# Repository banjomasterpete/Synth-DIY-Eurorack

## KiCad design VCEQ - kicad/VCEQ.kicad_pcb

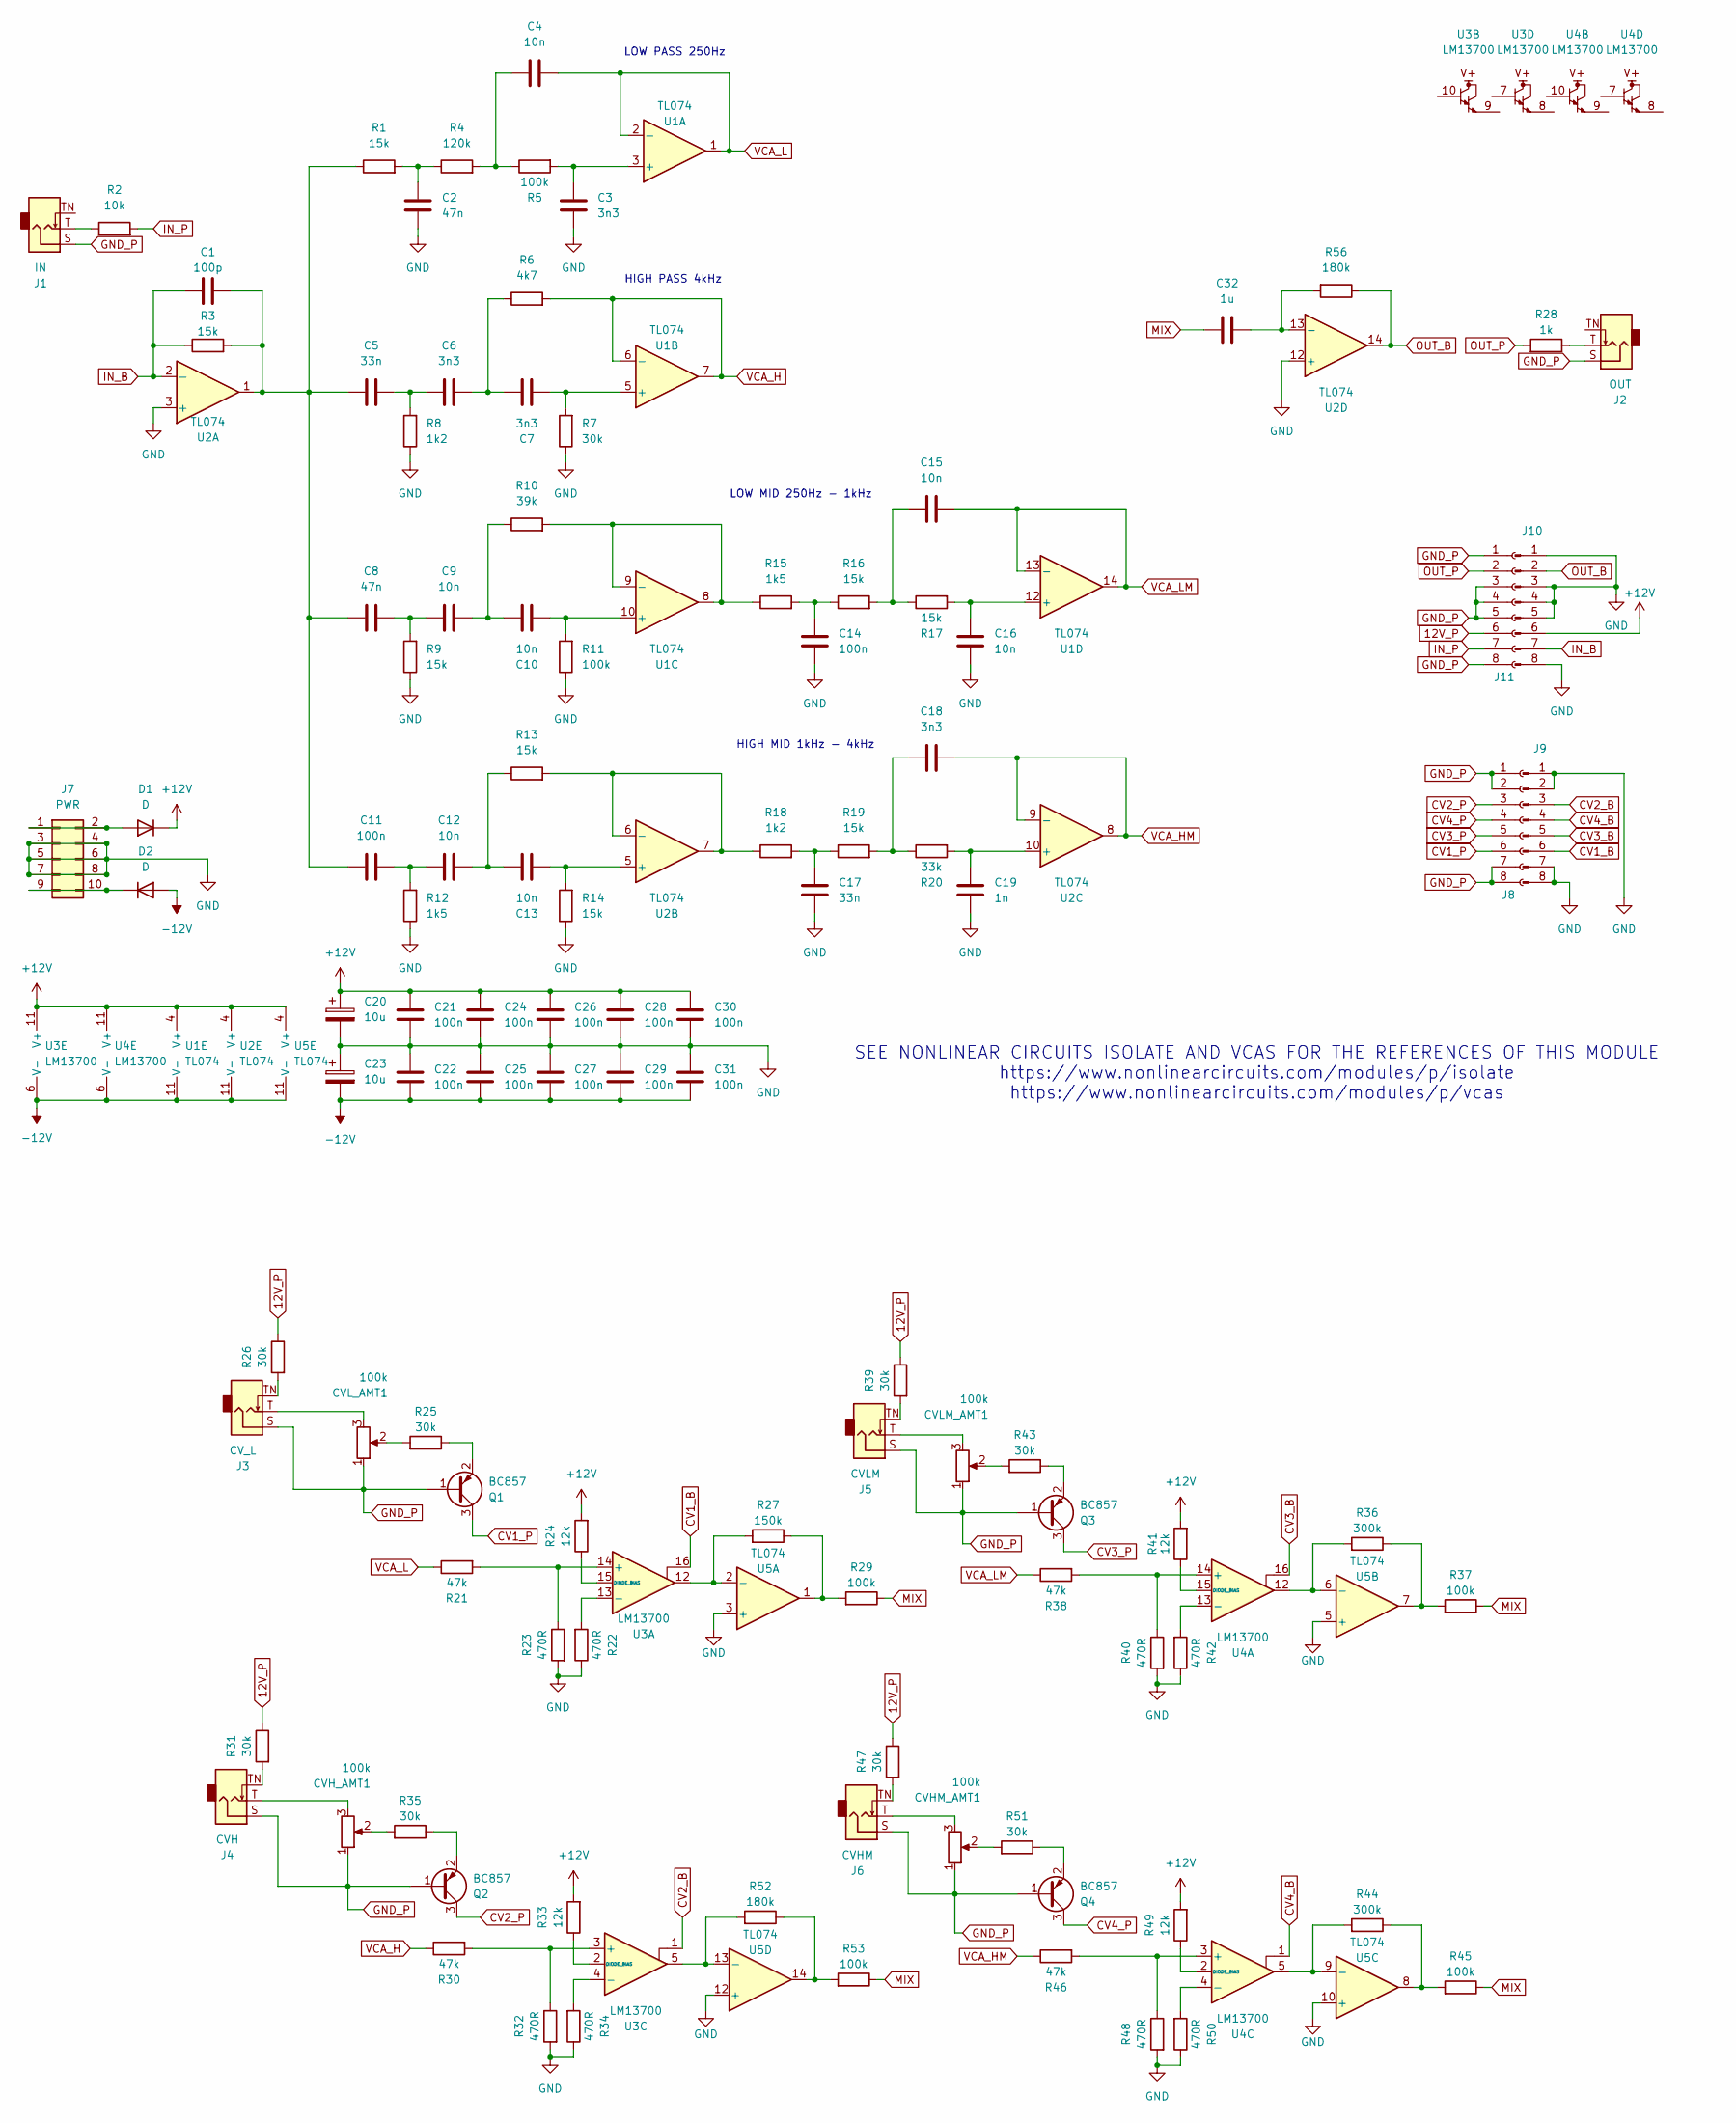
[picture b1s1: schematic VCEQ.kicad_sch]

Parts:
C1: 100p; C_0805_2012Metric_Pad1.18x1.45mm_HandSolder
C2, C8: 47n; C_0805_2012Metric_Pad1.18x1.45mm_HandSolder
C3, C6, C7, C18: 3n3; C_0805_2012Metric_Pad1.18x1.45mm_HandSolder
C4, C9, C10, C12, C13, C15, C16: 10n; C_0805_2012Metric_Pad1.18x1.45mm_HandSolder
C5, C17: 33n; C_0805_2012Metric_Pad1.18x1.45mm_HandSolder
C11, C14, C21, C22, C24, C25, C26, C27, C28, C29, C30, C31: 100n; C_0805_2012Metric_Pad1.18x1.45mm_HandSolder
C19: 1n; C_0805_2012Metric_Pad1.18x1.45mm_HandSolder
C20, C23: 10u; CP_Radial_D5.0mm_P2.50mm
C32: 1u; C_0805_2012Metric_Pad1.18x1.45mm_HandSolder
CVHM_AMT1: 100k; Potentiometer_Alps_RK09K_Single_Vertical
CVH_AMT1: 100k; Potentiometer_Alps_RK09K_Single_Vertical
CVLM_AMT1: 100k; Potentiometer_Alps_RK09K_Single_Vertical
CVL_AMT1: 100k; Potentiometer_Alps_RK09K_Single_Vertical
D1, D2: D; D_1210_3225Metric_Pad1.42x2.65mm_HandSolder
J1: IN; Jack_3.5mm_QingPu_WQP-PJ398SM_Vertical
J2: OUT; Jack_3.5mm_QingPu_WQP-PJ398SM_Vertical
J3: CV_L; Jack_3.5mm_QingPu_WQP-PJ398SM_Vertical
J4: CVH; Jack_3.5mm_QingPu_WQP-PJ398SM_Vertical
J5: CVLM; Jack_3.5mm_QingPu_WQP-PJ398SM_Vertical
J6: CVHM; Jack_3.5mm_QingPu_WQP-PJ398SM_Vertical
J7: PWR; PinHeader_2x05_P2.54mm_Vertical
J8, J11: PinHeader_1x08_P2.54mm_Vertical
J9, J10: Conn_01x08_Pin; PinHeader_1x08_P2.54mm_Vertical
Q1, Q2, Q3, Q4: BC857; SOT-23
R1, R3, R9, R13, R14, R16, R17, R19: 15k; R_0805_2012Metric_Pad1.20x1.40mm_HandSolder
R2: 10k; R_0805_2012Metric_Pad1.20x1.40mm_HandSolder
R4: 120k; R_0805_2012Metric_Pad1.20x1.40mm_HandSolder
R5, R11, R29, R37, R45, R53: 100k; R_0805_2012Metric_Pad1.20x1.40mm_HandSolder
R6: 4k7; R_0805_2012Metric_Pad1.20x1.40mm_HandSolder
R7, R25, R26, R31, R35, R39, R43, R47, R51: 30k; R_0805_2012Metric_Pad1.20x1.40mm_HandSolder
R8, R18: 1k2; R_0805_2012Metric_Pad1.20x1.40mm_HandSolder
R10: 39k; R_0805_2012Metric_Pad1.20x1.40mm_HandSolder
R12, R15: 1k5; R_0805_2012Metric_Pad1.20x1.40mm_HandSolder
R20: 33k; R_0805_2012Metric_Pad1.20x1.40mm_HandSolder
R21, R30, R38, R46: 47k; R_0805_2012Metric_Pad1.20x1.40mm_HandSolder
R22, R23, R32, R34, R40, R42, R48, R50: 470R; R_0805_2012Metric_Pad1.20x1.40mm_HandSolder
R24, R33, R41, R49: 12k; R_0805_2012Metric_Pad1.20x1.40mm_HandSolder
R27: 150k; R_0805_2012Metric_Pad1.20x1.40mm_HandSolder
R28: 1k; R_0805_2012Metric_Pad1.20x1.40mm_HandSolder
R36, R44: 300k; R_0805_2012Metric_Pad1.20x1.40mm_HandSolder
R52, R56: 180k; R_0805_2012Metric_Pad1.20x1.40mm_HandSolder
U1, U2, U5: TL074; SOIC-14_3.9x8.7mm_P1.27mm
U3, U4: LM13700; SOIC-16_3.9x9.9mm_P1.27mm

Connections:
12V_P: J11.6, R26.1, R31.1, R39.1, R47.1
+12V: C20.1, C21.2, C24.2, C26.2, C28.2, C30.2, D1.1 (K), J10.6, R24.2, R33.2, R41.2, R49.2, U1.4 (V+), U2.4 (V+), U3.11 (V+), U4.11 (V+), U5.4 (V+)
-12V: C22.1, C23.2, C25.1, C27.1, C29.1, C31.1, D2.2 (A), U1.11 (V-), U2.11 (V-), U3.6 (V-), U4.6 (V-), U5.11 (V-)
CV1_B: J9.6, U3.16
CV1_P: J8.6, Q1.3 (C)
CV2_B: J9.3, U3.1
CV2_P: J8.3, Q2.3 (C)
CV3_B: J9.5, U4.16
CV3_P: J8.5, Q3.3 (C)
CV4_B: J9.4, U4.1
CV4_P: J8.4, Q4.3 (C)
GND: C2.1, C3.1, C14.1, C16.1, C17.1, C19.1, C20.2, C21.1, C22.2, C23.1, C24.1, C25.2, C26.1, C27.2, C28.1, C29.2, C30.1, C31.2, J7.3, J7.4, J7.5, J7.6, J7.7, J7.8, J9.1, J9.2, J9.7, J9.8, J10.1, J10.3, J10.4, J10.5, J10.8, R7.1, R8.1, R9.1, R11.1, R12.1, R14.1, R22.1, R23.2, R32.2, R34.1, R40.2, R42.1, R48.2, R50.1, U2.3 (+), U2.12 (+), U5.3 (+), U5.5 (+), U5.10 (+), U5.12 (+)
GND_P: CVHM_AMT1.1, CVH_AMT1.1, CVLM_AMT1.1, CVL_AMT1.1, J1.S, J2.S, J3.S, J4.S, J5.S, J6.S, J8.1, J8.2, J8.7, J8.8, J11.1, J11.3, J11.4, J11.5, J11.8, Q1.1 (B), Q2.1 (B), Q3.1 (B), Q4.1 (B)
IN_B: C1.1, J10.7, R3.1, U2.2 (-)
IN_P: J11.7, R2.2
MIX: C32.2, R29.1, R37.1, R45.1, R53.1
unnamed: C1.2, C5.2, C8.2, C11.2, R1.1, R3.2, U2.1
unnamed: C2.2, R1.2, R4.1
unnamed: C4.2, R4.2, R5.1
unnamed: C5.1, C6.2, R8.2
unnamed: C6.1, C7.2, R6.1
unnamed: C8.1, C9.2, R9.2
unnamed: C9.1, C10.2, R10.1
unnamed: C11.1, C12.2, R12.2
unnamed: C12.1, C13.2, R13.1
unnamed: C14.2, R15.2, R16.1
unnamed: C15.2, R16.2, R17.1
unnamed: C17.2, R18.2, R19.1
unnamed: C18.2, R19.2, R20.1
unnamed: CVHM_AMT1.2, R51.2
unnamed: CVHM_AMT1.3, J6.T
unnamed: CVH_AMT1.2, R35.2
unnamed: CVH_AMT1.3, J4.T
unnamed: CVLM_AMT1.2, R43.2
unnamed: CVLM_AMT1.3, J5.T
unnamed: CVL_AMT1.2, R25.2
unnamed: CVL_AMT1.3, J3.T
unnamed: D1.2 (A), J7.1, J7.2
unnamed: D2.1 (K), J7.9, J7.10
unnamed: J1.T, R2.1
unnamed: J2.T, R28.1
unnamed: J3.TN, R26.2
unnamed: J4.TN, R31.2
unnamed: J5.TN, R39.2
unnamed: J6.TN, R47.2
unnamed: Q1.2 (E), R25.1
unnamed: Q2.2 (E), R35.1
unnamed: Q3.2 (E), R43.1
unnamed: Q4.2 (E), R51.1
unnamed: R27.1, R29.2, U5.1
unnamed: R36.1, R37.2, U5.7
unnamed: R44.1, R45.2, U5.8
unnamed: R52.1, R53.2, U5.14
unnamed: C3.2, R5.2, U1.3 (+)
unnamed: C7.1, R7.2, U1.5 (+)
unnamed: C10.1, R11.2, U1.10 (+)
unnamed: R10.2, R15.1, U1.8, U1.9 (-)
unnamed: C16.2, R17.2, U1.12 (+)
unnamed: C13.1, R14.2, U2.5 (+)
unnamed: R13.2, R18.1, U2.6 (-), U2.7
unnamed: C19.2, R20.2, U2.10 (+)
unnamed: C32.1, R56.2, U2.13 (-)
unnamed: R21.2, R23.1, U3.14 (+)
unnamed: R22.2, U3.13 (-)
unnamed: R24.1, U3.15 (DIODE_BIAS)
unnamed: R30.2, R32.1, U3.3 (+)
unnamed: R34.2, U3.4 (-)
unnamed: R33.1, U3.2 (DIODE_BIAS)
unnamed: R38.2, R40.1, U4.14 (+)
unnamed: R42.2, U4.13 (-)
unnamed: R41.1, U4.15 (DIODE_BIAS)
unnamed: R46.2, R48.1, U4.3 (+)
unnamed: R50.2, U4.4 (-)
unnamed: R49.1, U4.2 (DIODE_BIAS)
unnamed: R27.2, U3.12, U5.2 (-)
unnamed: R36.2, U4.12, U5.6 (-)
unnamed: R44.2, U4.5, U5.9 (-)
unnamed: R52.2, U3.5, U5.13 (-)
OUT_B: J10.2, R56.1, U2.14
OUT_P: J11.2, R28.2
VCA_H: R6.2, R30.1, U1.6 (-), U1.7
VCA_HM: C18.1, R46.1, U2.8, U2.9 (-)
VCA_L: C4.1, R21.1, U1.1, U1.2 (-)
VCA_LM: C15.1, R38.1, U1.13 (-), U1.14

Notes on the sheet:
LOW PASS 250Hz
HIGH MID 1kHz - 4kHz
LOW MID 250Hz - 1kHz
SEE NONLINEAR CIRCUITS ISOLATE AND VCAS FOR THE REFERENCES OF THIS MODULE https://www.nonlinearcircuits.com/modules/p/isolate https://www.nonlinearcircuits.com/modules/p/vcas
HIGH PASS 4kHz

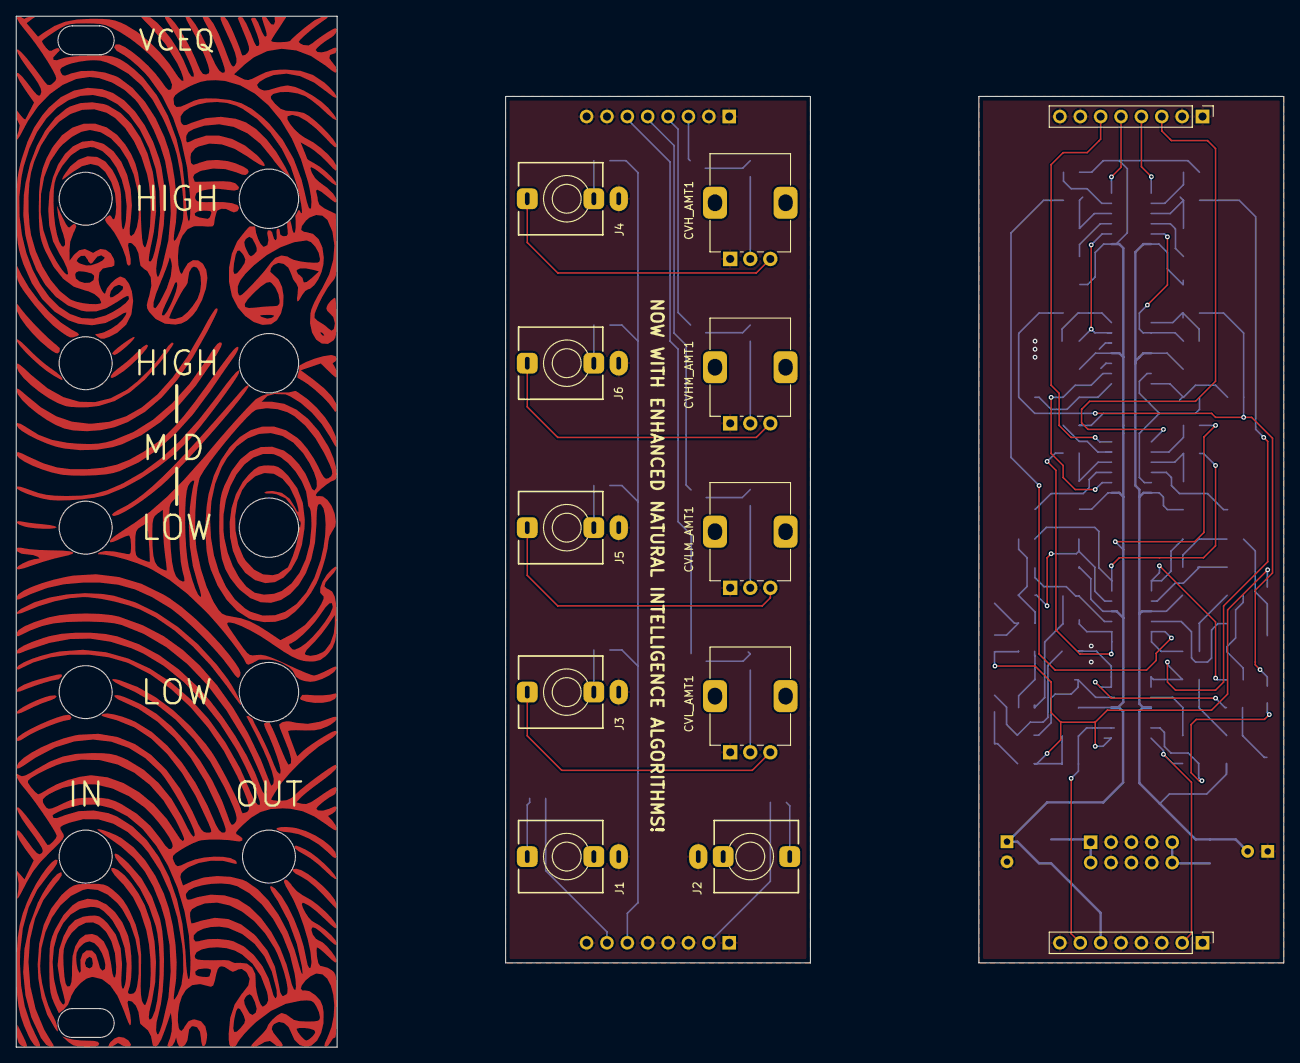
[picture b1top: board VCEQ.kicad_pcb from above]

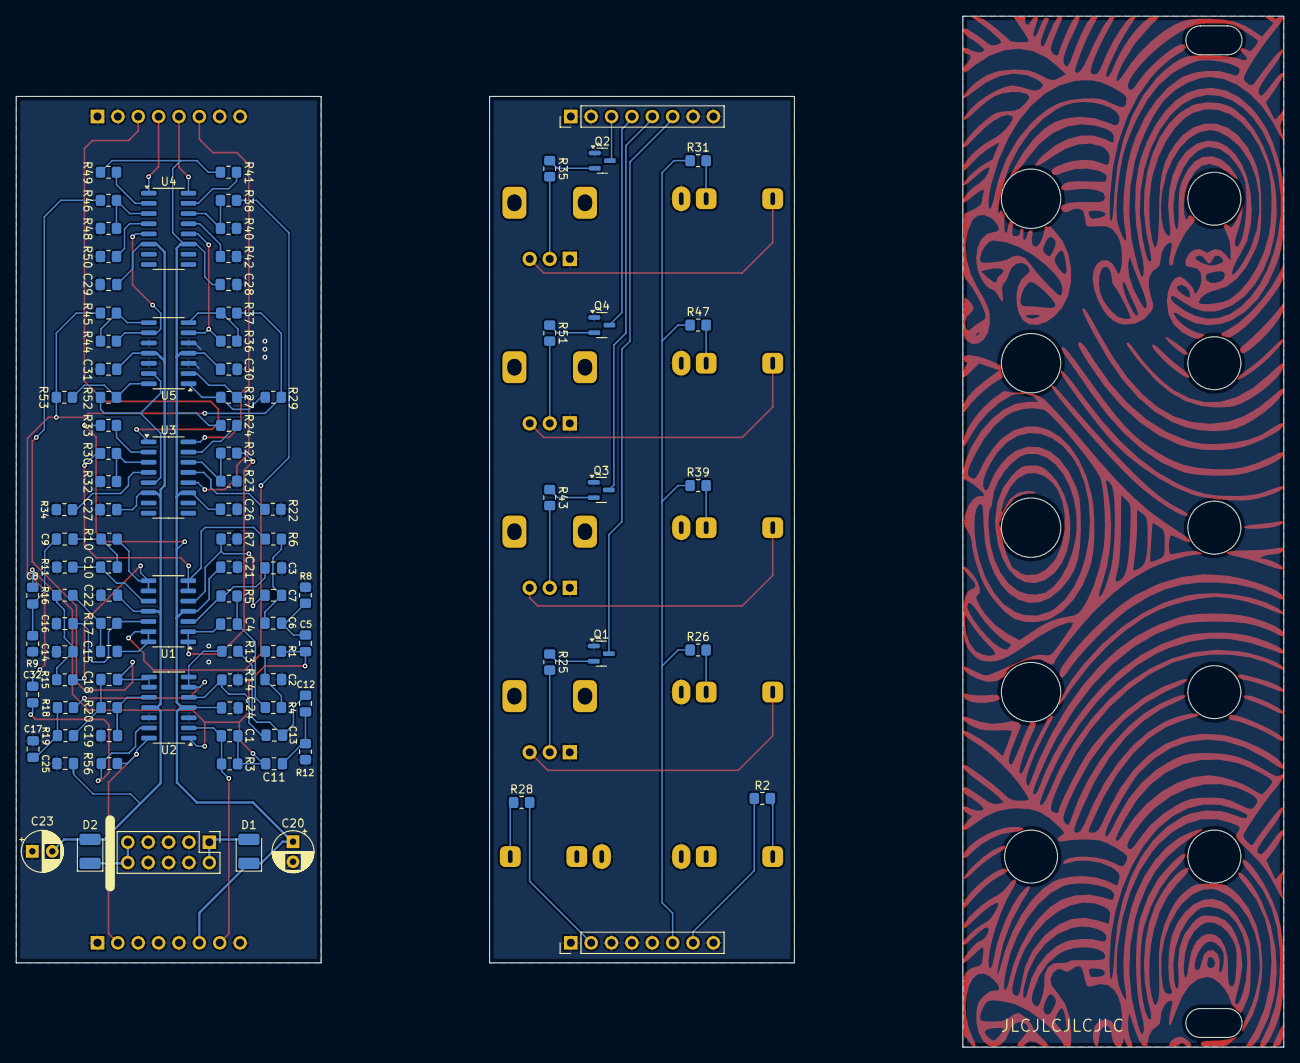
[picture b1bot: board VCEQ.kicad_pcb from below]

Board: 2 copper layers, 158.0 x 128.5 mm, 112 parts (100 on the bottom side), 84 nets.

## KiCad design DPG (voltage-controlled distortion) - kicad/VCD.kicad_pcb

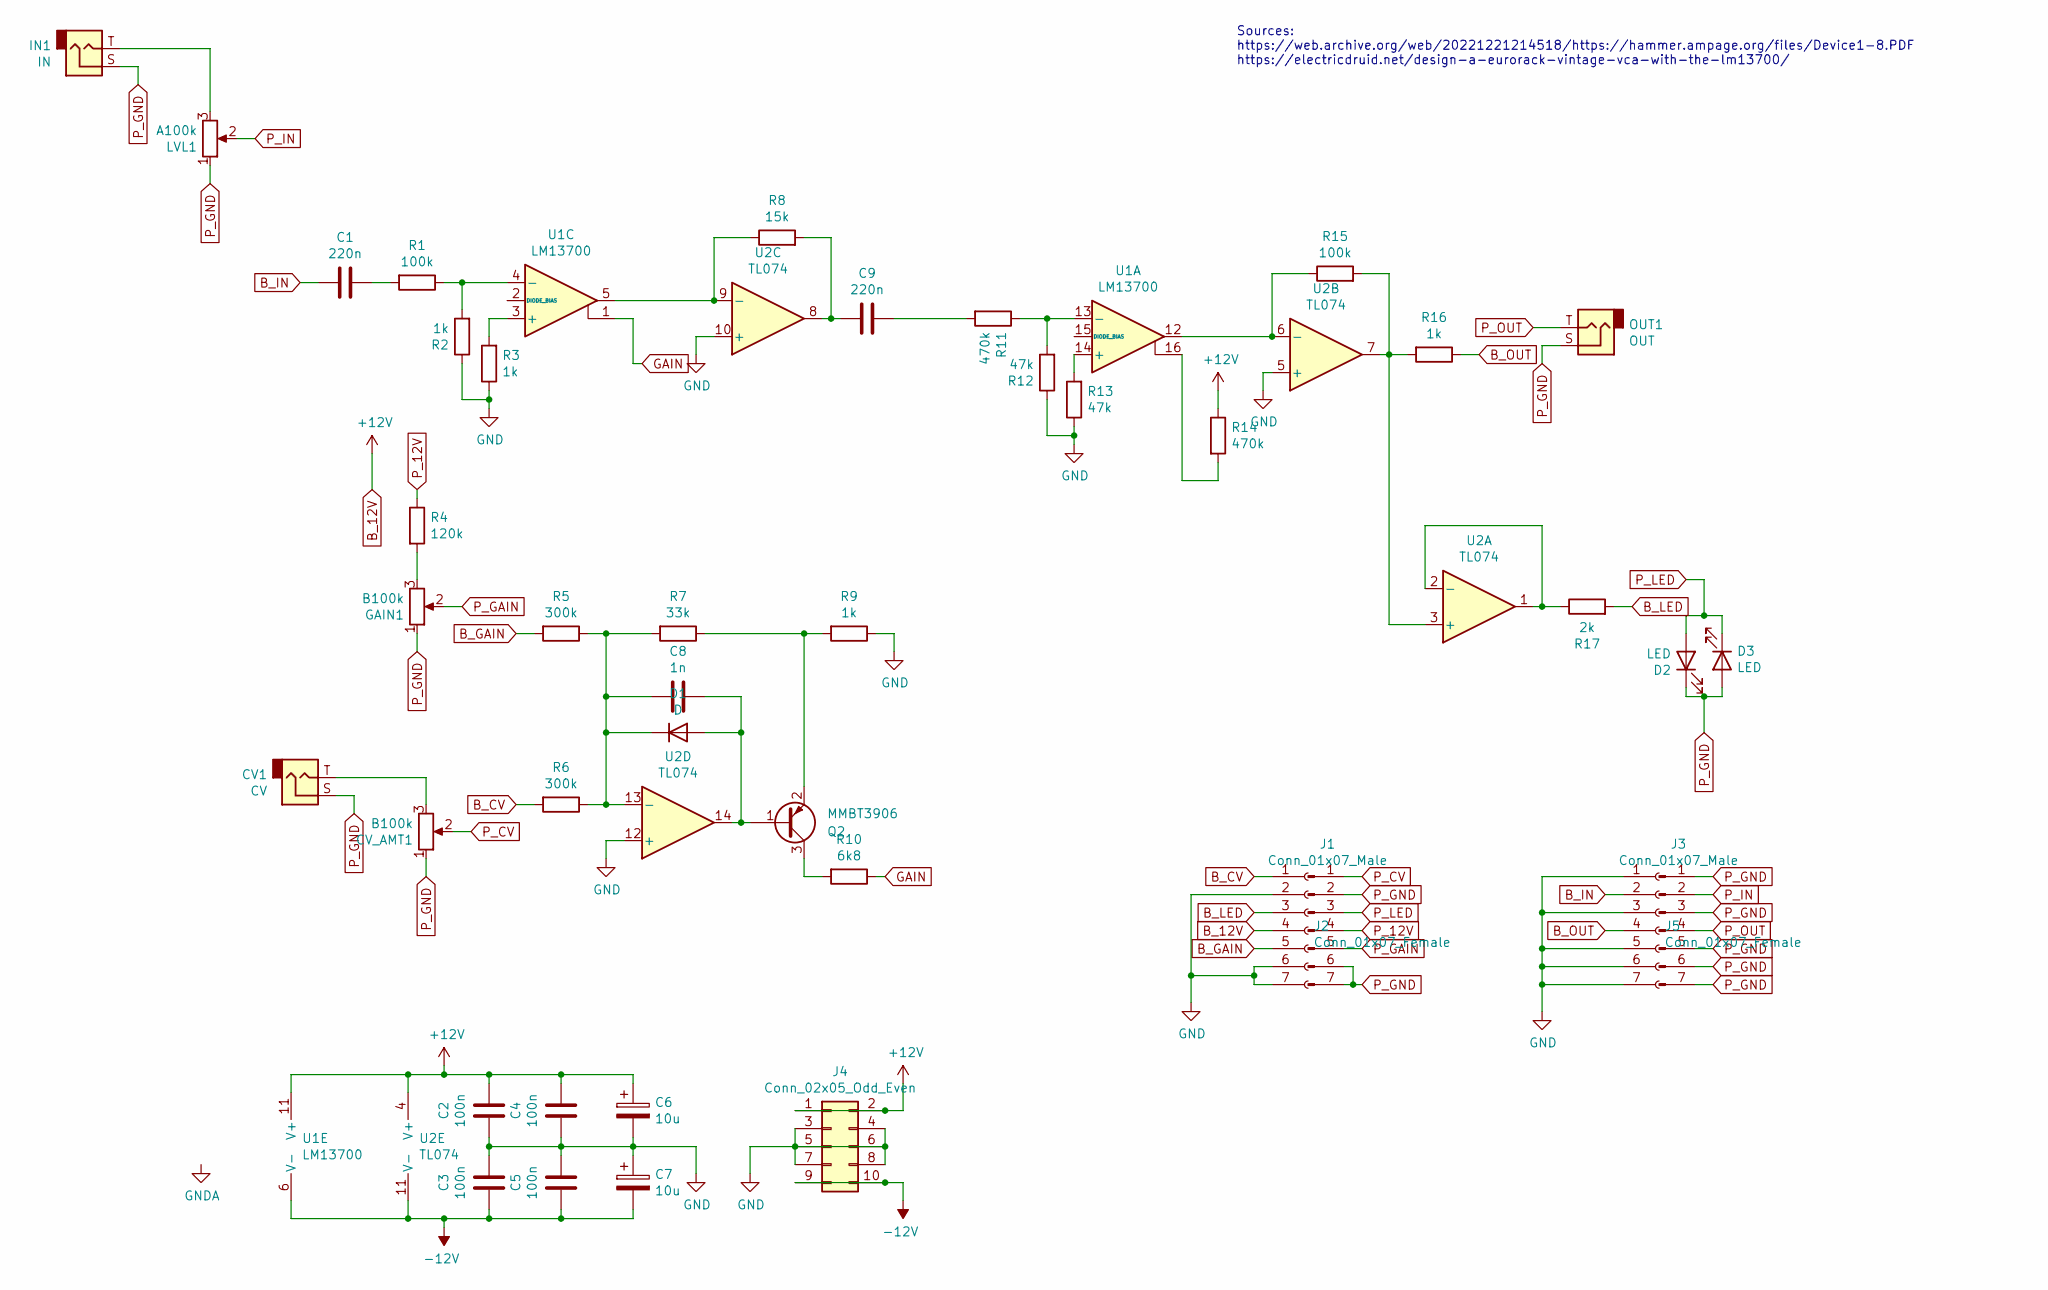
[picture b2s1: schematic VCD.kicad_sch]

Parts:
C1, C9: 220n; C_0805_2012Metric_Pad1.18x1.45mm_HandSolder
C2, C3, C4, C5: 100n; C_0805_2012Metric_Pad1.18x1.45mm_HandSolder
C6, C7: 10u; CP_Radial_D5.0mm_P2.50mm
C8: 1n; C_0805_2012Metric_Pad1.18x1.45mm_HandSolder
CV1: CV; Jack_3.5mm_QingPu_WQP-PJ366ST_Vertical
CV_AMT1: B100k; Potentiometer_Alpha_RD901F-40-00D_Single_Vertical
D1: D; D_SOD-323_HandSoldering
D2, D3: LED; LED_D3.0mm
GAIN1: B100k; Potentiometer_Alpha_RD901F-40-00D_Single_Vertical
IN1: IN; Jack_3.5mm_QingPu_WQP-PJ366ST_Vertical
J1, J3: Conn_01x07_Male; PinHeader_1x07_P2.54mm_Vertical
J2, J5: Conn_01x07_Female; PinHeader_1x07_P2.54mm_Vertical
J4: Conn_02x05_Odd_Even; PinHeader_2x05_P2.54mm_Vertical
LVL1: A100k; Potentiometer_Alpha_RD901F-40-00D_Single_Vertical
OUT1: OUT; Jack_3.5mm_QingPu_WQP-PJ366ST_Vertical
Q2: MMBT3906; SOT-23
R1, R15: 100k; R_0805_2012Metric_Pad1.20x1.40mm_HandSolder
R2, R3, R9, R16: 1k; R_0805_2012Metric_Pad1.20x1.40mm_HandSolder
R4: 120k; R_0805_2012Metric_Pad1.20x1.40mm_HandSolder
R5, R6: 300k; R_0805_2012Metric_Pad1.20x1.40mm_HandSolder
R7: 33k; R_0805_2012Metric_Pad1.20x1.40mm_HandSolder
R8: 15k; R_0805_2012Metric_Pad1.20x1.40mm_HandSolder
R10: 6k8; R_0805_2012Metric_Pad1.20x1.40mm_HandSolder
R11, R14: 470k; R_0805_2012Metric_Pad1.20x1.40mm_HandSolder
R12, R13: 47k; R_0805_2012Metric_Pad1.20x1.40mm_HandSolder
R17: 2k; R_0805_2012Metric_Pad1.20x1.40mm_HandSolder
U1: LM13700; SOIC-16_3.9x9.9mm_P1.27mm
U2: TL074; SOIC-14_3.9x8.7mm_P1.27mm

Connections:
-12V: C3.2, C5.2, C7.2, J4.9, J4.10, U1.6 (V-), U2.11 (V-)
B_12V: C2.1, C4.1, C6.1, J2.4, J4.1, J4.2, R14.1, U1.11 (V+), U2.4 (V+)
B_CV: J2.1, R6.2
B_GAIN: J2.5, R5.2
B_IN: C1.2, J5.2
B_LED: J2.3, R17.2
B_OUT: J5.4, R16.1
GAIN: R10.1, U1.1
GND: C2.2, C3.1, C4.2, C5.1, C6.2, C7.1, J2.2, J2.6, J2.7, J4.3, J4.4, J4.5, J4.6, J4.7, J4.8, J5.1, J5.3, J5.5, J5.6, J5.7, R2.1, R3.1, R9.1, R12.1, R13.1, U2.5 (+), U2.10 (+), U2.12 (+)
unnamed: C1.1, R1.2
unnamed: C9.1, R11.2
unnamed: C9.2, R8.2, U2.8
unnamed: CV1.T, CV_AMT1.3
unnamed: C8.1, D1.2 (A), Q2.1 (B), U2.14
unnamed: C8.2, D1.1 (K), R5.1, R6.1, R7.2, U2.13 (-)
unnamed: GAIN1.3, R4.2
unnamed: IN1.T, LVL1.3
unnamed: Q2.3 (C), R10.2
unnamed: Q2.2 (E), R7.1, R9.2
unnamed: R14.2, U1.16
unnamed: R13.2, U1.14 (+)
unnamed: R11.1, R12.2, U1.13 (-)
unnamed: R3.2, U1.3 (+)
unnamed: R1.1, R2.2, U1.4 (-)
unnamed: R15.2, R16.2, U2.3 (+), U2.7
unnamed: R17.1, U2.1, U2.2 (-)
unnamed: R15.1, U1.12, U2.6 (-)
unnamed: R8.1, U1.5, U2.9 (-)
P_12V: J1.4, R4.1
P_CV: CV_AMT1.2, J1.1
P_GAIN: GAIN1.2, J1.5
P_GND: CV1.S, CV_AMT1.1, D2.1 (K), D3.2 (A), GAIN1.1, IN1.S, J1.2, J1.6, J1.7, J3.1, J3.3, J3.5, J3.6, J3.7, LVL1.1, OUT1.S
P_IN: J3.2, LVL1.2
P_LED: D2.2 (A), D3.1 (K), J1.3
P_OUT: J3.4, OUT1.T

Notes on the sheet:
Sources: https://web.archive.org/web/20221221214518/https://hammer.ampage.org/files/Device1-8.PDF https://electricdruid.net/design-a-eurorack-vintage-vca-with-the-lm13700/

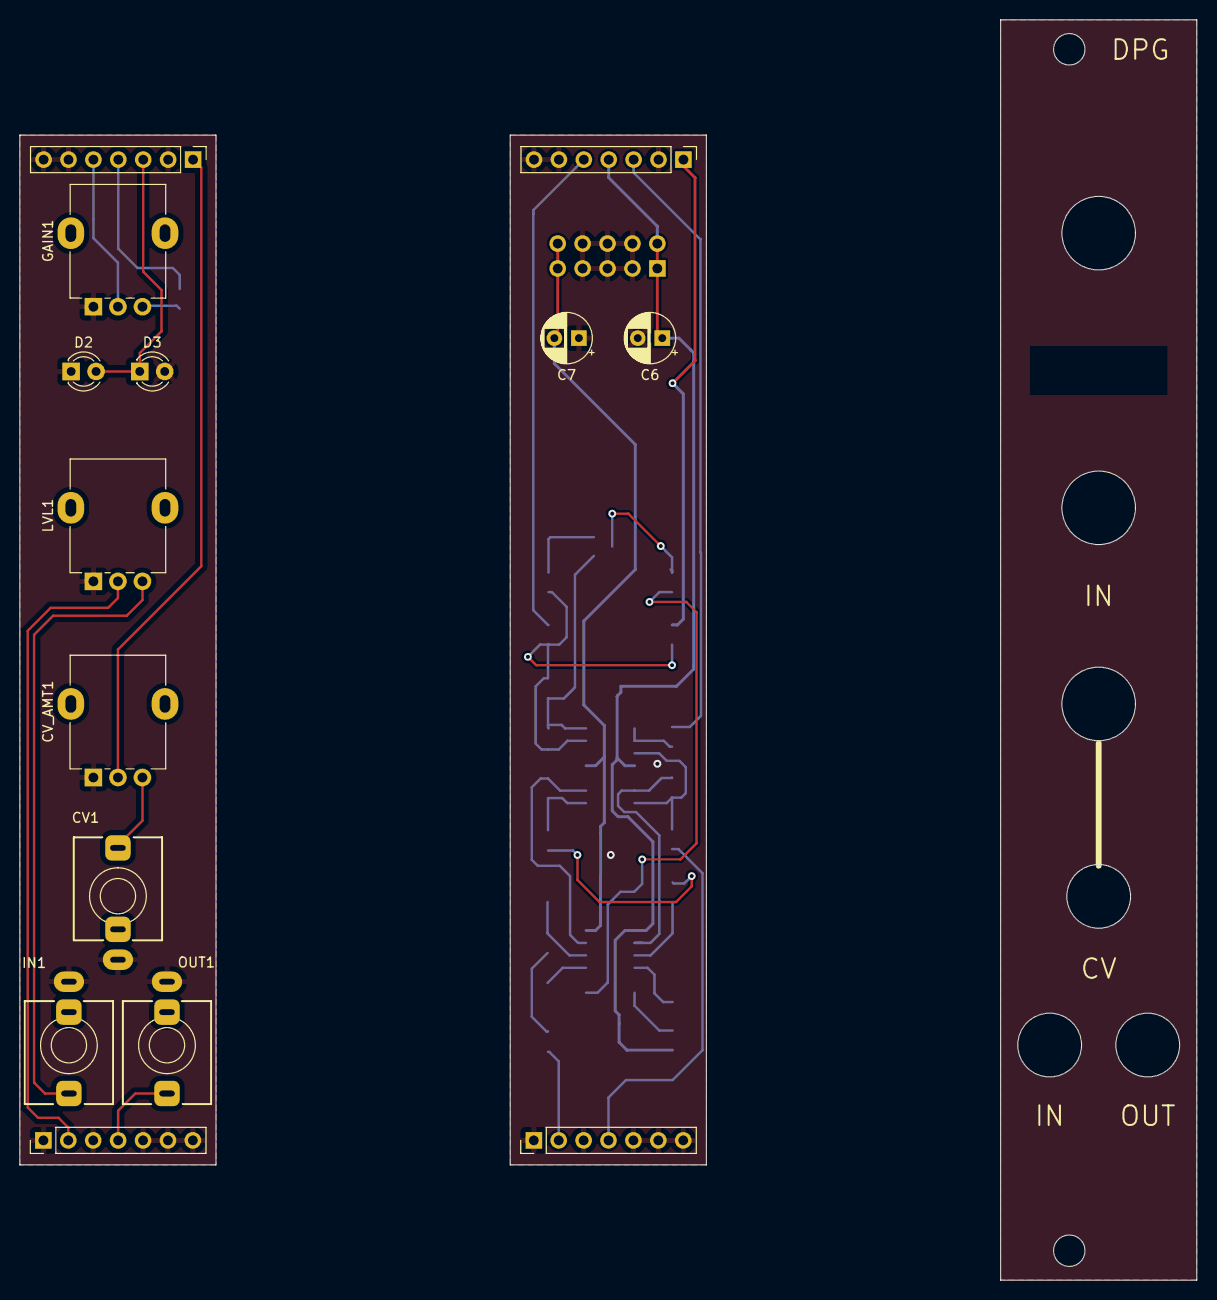
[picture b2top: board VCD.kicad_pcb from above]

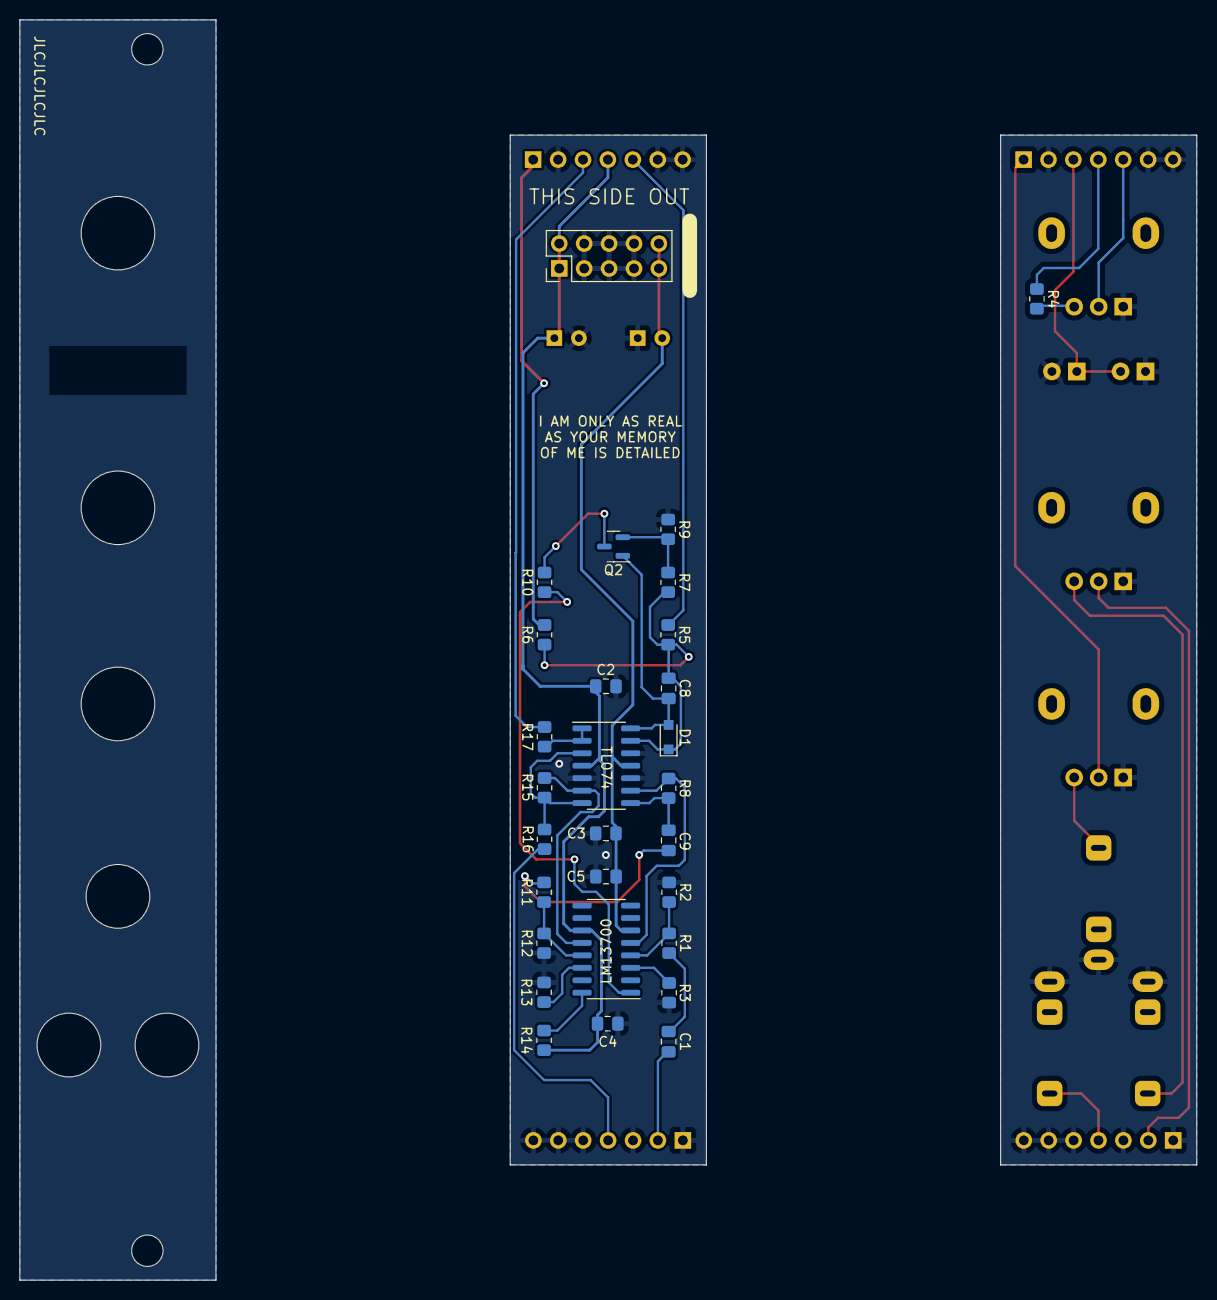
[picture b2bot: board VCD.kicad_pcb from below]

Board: 2 copper layers, 120.0 x 128.5 mm, 43 parts (29 on the bottom side), 35 nets.

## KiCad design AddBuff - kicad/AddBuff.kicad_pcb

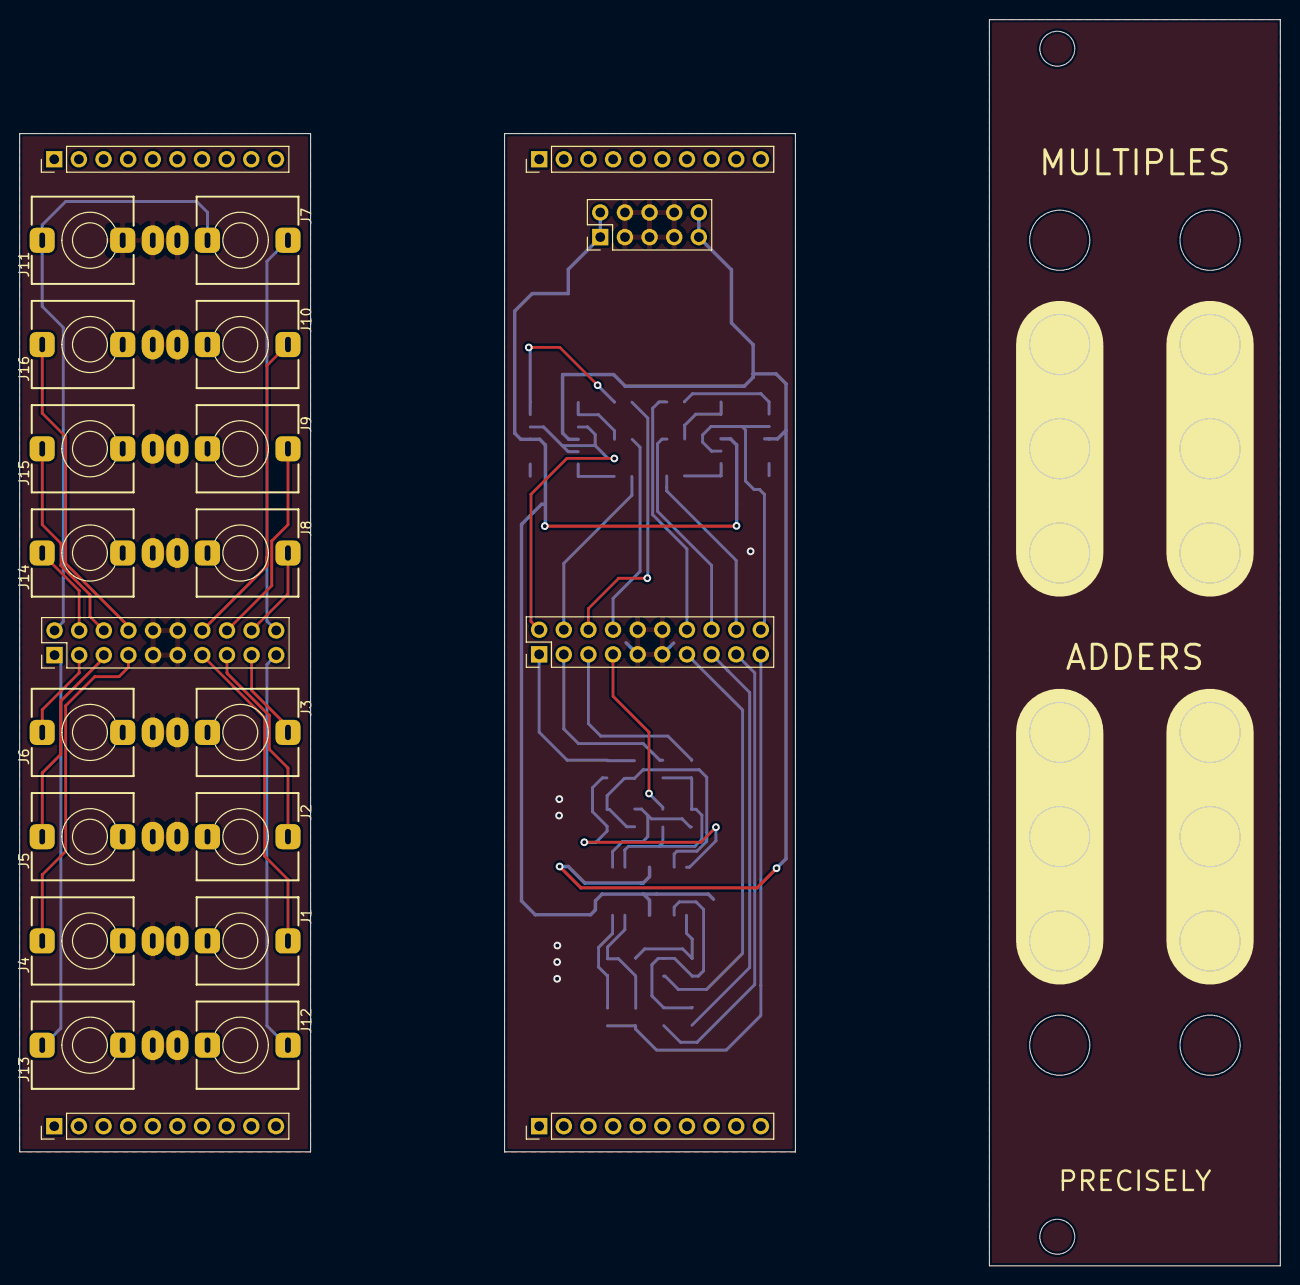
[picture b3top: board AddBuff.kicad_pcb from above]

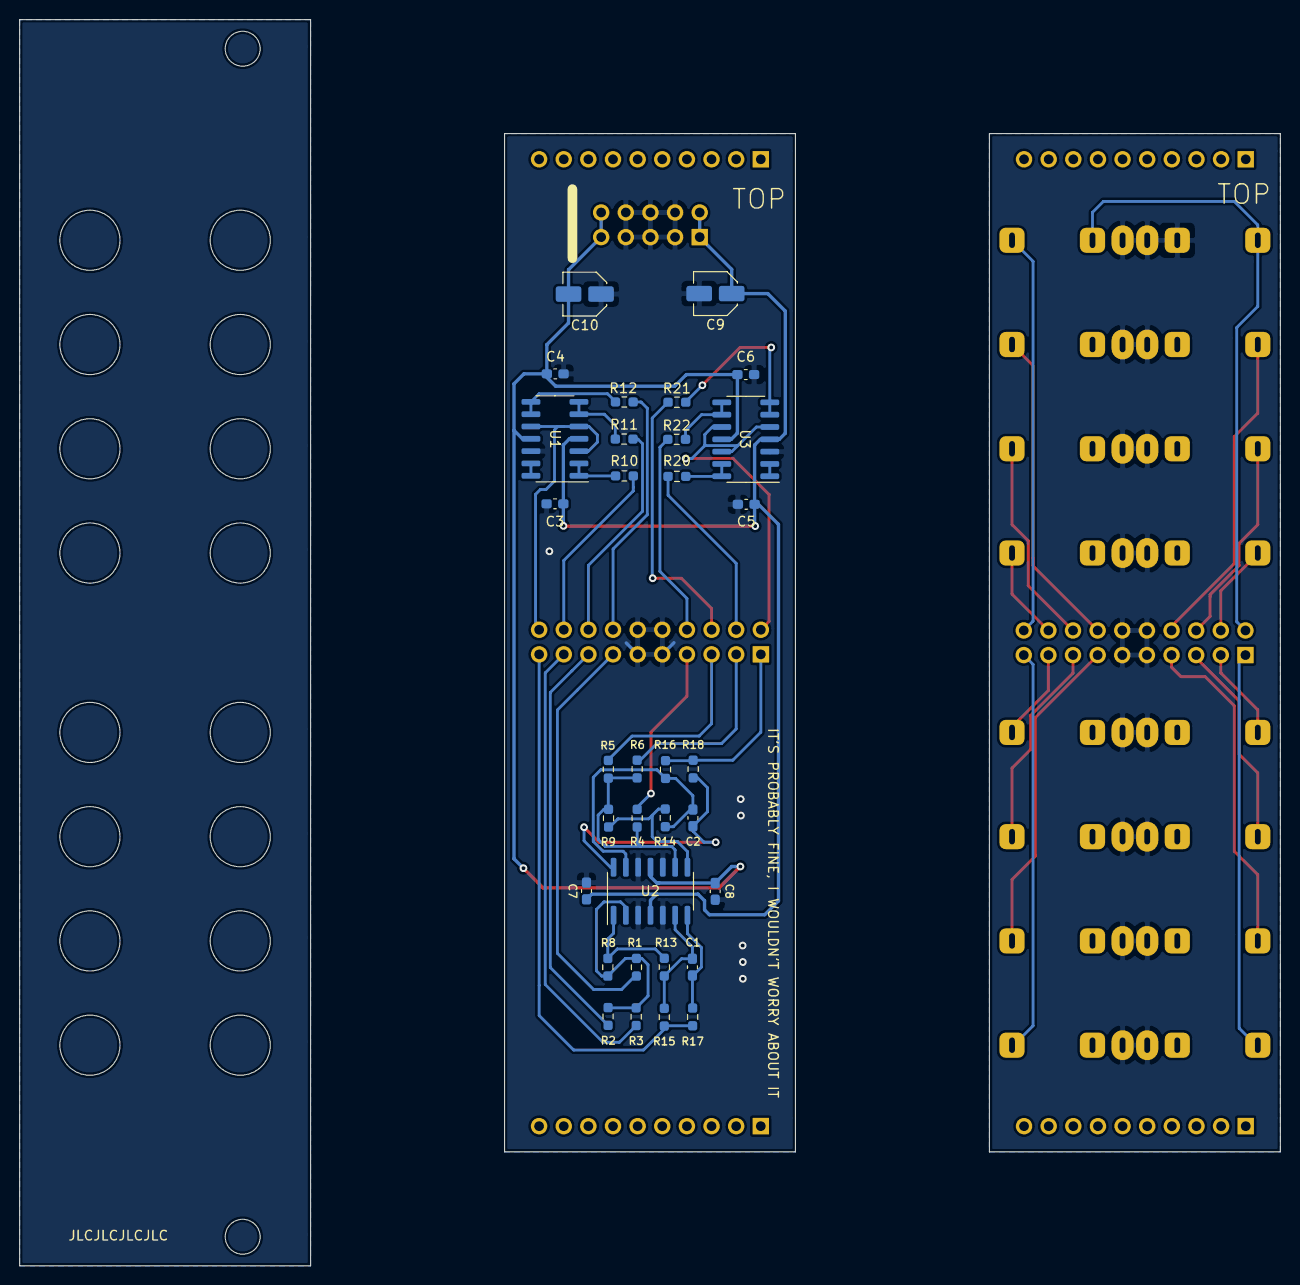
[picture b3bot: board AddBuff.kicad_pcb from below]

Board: 2 copper layers, 130.0 x 128.5 mm, 56 parts (33 on the bottom side), 52 nets.

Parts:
C1, C2: 47p; C_0603_1608Metric_Pad1.08x0.95mm_HandSolder
C3, C4, C5, C6, C7, C8: 100n; C_0603_1608Metric_Pad1.08x0.95mm_HandSolder
C9, C10: 10u; C_Elec_4x5.4
J1, J2, J3, J4, J5, J6, J7, J8, J9, J10, J11, J12, J13, J14, J15, J16: AudioJack2_SwitchT; Jack_3.5mm_QingPu_WQP-PJ398SM_Vertical
J17: Conn_02x05_Odd_Even; PinHeader_2x05_P2.54mm_Vertical
J18, J19: Conn_02x10_Odd_Even; PinHeader_2x10_P2.54mm_Vertical
J20, J22: Conn_01x10_Female; PinHeader_1x10_P2.54mm_Vertical
J21, J23: Conn_01x10_Male; PinHeader_1x10_P2.54mm_Vertical
R1, R2, R3, R4, R5, R6, R8, R9, R13, R14, R15, R16: 100k; R_0603_1608Metric_Pad0.98x0.95mm_HandSolder
R10, R11, R12, R17, R18, R20, R21, R22: 100R; R_0603_1608Metric_Pad0.98x0.95mm_HandSolder
U1, U2, U3: TL074; SOIC-14_3.9x8.7mm_P1.27mm

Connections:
1INMLT_B: J19.20, U1.3, U1.5, U1.10
1INMLT_P: J7.T, J18.20
1MOUT_B: J19.18, R10.1
1MOUT_P: J8.T, J18.18
2IN1_B: J19.7, R4.2
2IN1_P: J4.T, J18.7
2IN2_B: J19.5, R5.2
2IN2_P: J5.T, J18.5
2IN3_B: J19.3, R6.2
2IN3_P: J6.T, J18.3
2INMLT_B: J19.2, U3.5, U3.10, U3.12
2INMLT_P: J7.TN, J11.T, J18.2
2MOUT_B: J19.16, R11.1
2MOUT_P: J9.T, J18.16
2OUT_B: J19.1, R16.1, R18.1
2OUT_P: J13.T, J18.1
3MOUT_B: J19.14, R12.1
3MOUT_P: J10.T, J18.14
4MOUT_B: J19.4, R20.1
4MOUT_P: J14.T, J18.4
5MOUT_B: J19.6, R21.1
5MOUT_P: J15.T, J18.6
6MOUT_B: J19.8, R22.1
6MOUT_P: J16.T, J18.8
+12V: C3.1, C5.1, C7.1, C9.1, J17.1, J17.2, U1.4, U2.4, U3.4
-12V: C4.2, C6.2, C8.2, C10.2, J17.9, J17.10, U1.11, U2.11, U3.11
GND: C3.2, C4.1, C5.2, C6.1, C7.2, C8.1, C9.2, C10.1, J17.3, J17.4, J17.5, J17.6, J17.7, J17.8, J19.9, J19.10, J19.11, J19.12, U1.12, U2.3, U2.5, U2.10, U2.12, U3.3
GND_P: J1.S, J2.S, J3.S, J4.S, J5.S, J6.S, J7.S, J8.S, J9.S, J10.S, J11.S, J11.TN, J12.S, J13.S, J14.S, J15.S, J16.S, J18.9, J18.10, J18.11, J18.12
IN1_B: J19.13, R1.2
IN1_P: J1.T, J18.13
IN2_B: J19.15, R2.2
IN2_P: J2.T, J18.15
IN3_B: J19.17, R3.2
IN3_P: J3.T, J18.17
unnamed: C1.1, R17.2, U2.7
unnamed: C1.2, R13.1, R15.2, U2.6
unnamed: C2.1, R18.2, U2.14
unnamed: C2.2, R14.1, R16.2, U2.13
unnamed: R1.1, R2.1, R3.1, R8.2, U2.2
unnamed: R4.1, R5.1, R6.1, R9.2, U2.9
unnamed: R10.2, U1.1, U1.2
unnamed: R11.2, U1.6, U1.7
unnamed: R12.2, U1.8, U1.9
unnamed: R8.1, R13.2, U2.1
unnamed: R9.1, R14.2, U2.8
unnamed: R20.2, U3.13, U3.14
unnamed: R21.2, U3.6, U3.7
unnamed: R22.2, U3.8, U3.9
unnamed: U1.13, U1.14
unnamed: U3.1, U3.2
OUT_B: J19.19, R15.1, R17.1
OUT_P: J12.T, J18.19
